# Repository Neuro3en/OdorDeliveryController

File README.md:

# OdorDeliveryController
Arduino shield for odor valve controller

This repo contains the PCB eagle files and the CAM files.
The Arduino code running on the µC

The related research:
https://www.cell.com/cell-reports/pdf/S2211-1247%2820%2930120-0.pdf

Both codes have three program options, identified on the arduino by LED1 ON, LED2 ON, LED1 and 2 ON.
in the script _3odors the three programs indicate the usage of the three odor valves (thus the use of three odors)
in the script A_B_AB, the three programs indicate the usage of valve/odor A, of valve/odor B, and of simultaneous usage of valves/odors AB

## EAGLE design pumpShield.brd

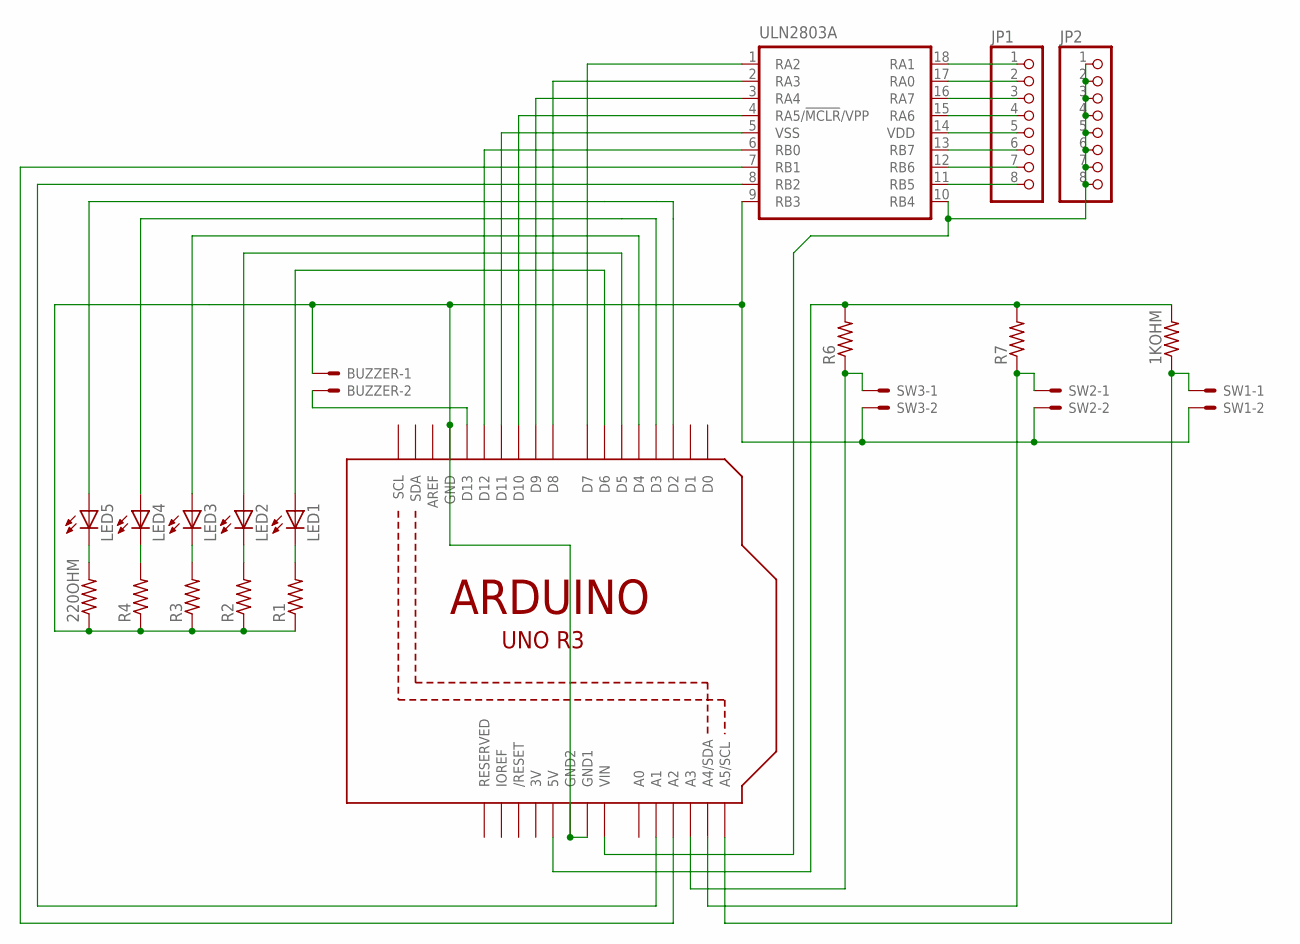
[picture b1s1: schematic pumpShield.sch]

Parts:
1KOHM, 220OHM: R-US_0207/9; 0207/9
BUZZER: 22-23-2021
JP1, JP2: PINHD-1X8CLEANBIG; 1X08-CLEANBIG
LED1, LED2, LED3, LED4, LED5: LED3MM
R1, R2, R3, R4, R6, R7: R-US_0207/9; 0207/9
SW1, SW2, SW3: 22-23-2021
U1: ARDUINOR3-DIMENSION; ARDUINOR3
ULN2803A: PIC16F1826/27P; DIL18

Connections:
3V: U1.3V
unnamed: 220OHM.1, BUZZER.1, R1.1, R2.1, R3.1, R4.1, SW1.2, SW2.2, SW3.2, U1.GND, U1.GND1, U1.GND2, ULN2803A.9 (RB3)
unnamed: JP2.1, JP2.2, JP2.3, JP2.4, JP2.5, JP2.6, JP2.7, JP2.8, U1.VIN, ULN2803A.10 (RB4)
unnamed: LED1.A, U1.D6
unnamed: LED2.A, U1.D5
unnamed: LED3.A, U1.D4
unnamed: LED4.A, U1.D3
unnamed: U1.D7, ULN2803A.1 (RA2)
unnamed: U1.D8, ULN2803A.2 (RA3)
unnamed: U1.D9, ULN2803A.3 (RA4)
unnamed: U1.D10, ULN2803A.4 (RA5/!MCLR!/VPP)
unnamed: U1.D11, ULN2803A.5 (VSS)
unnamed: U1.D12, ULN2803A.6 (RB0)
unnamed: LED1.K (C), R1.2
unnamed: LED2.K (C), R2.2
unnamed: LED3.K (C), R3.2
unnamed: LED4.K (C), R4.2
unnamed: 220OHM.2, LED5.K (C)
unnamed: LED5.A, U1.D2
unnamed: BUZZER.2, U1.D13
unnamed: 1KOHM.2, R6.2, R7.2, U1.5V
unnamed: JP1.8, ULN2803A.11 (RB5)
unnamed: JP1.7, ULN2803A.12 (RB6)
unnamed: JP1.6, ULN2803A.13 (RB7)
unnamed: JP1.5, ULN2803A.14 (VDD)
unnamed: JP1.4, ULN2803A.15 (RA6)
unnamed: JP1.3, ULN2803A.16 (RA7)
unnamed: R6.1, SW3.1, U1.A3
unnamed: R7.1, SW2.1, U1.A4 (A4/SDA)
unnamed: 1KOHM.1, SW1.1, U1.A5 (A5/SCL)
unnamed: U1.A1, ULN2803A.8 (RB2)
unnamed: U1.A2, ULN2803A.7 (RB1)
unnamed: JP1.2, ULN2803A.17 (RA0)
unnamed: JP1.1, ULN2803A.18 (RA1)

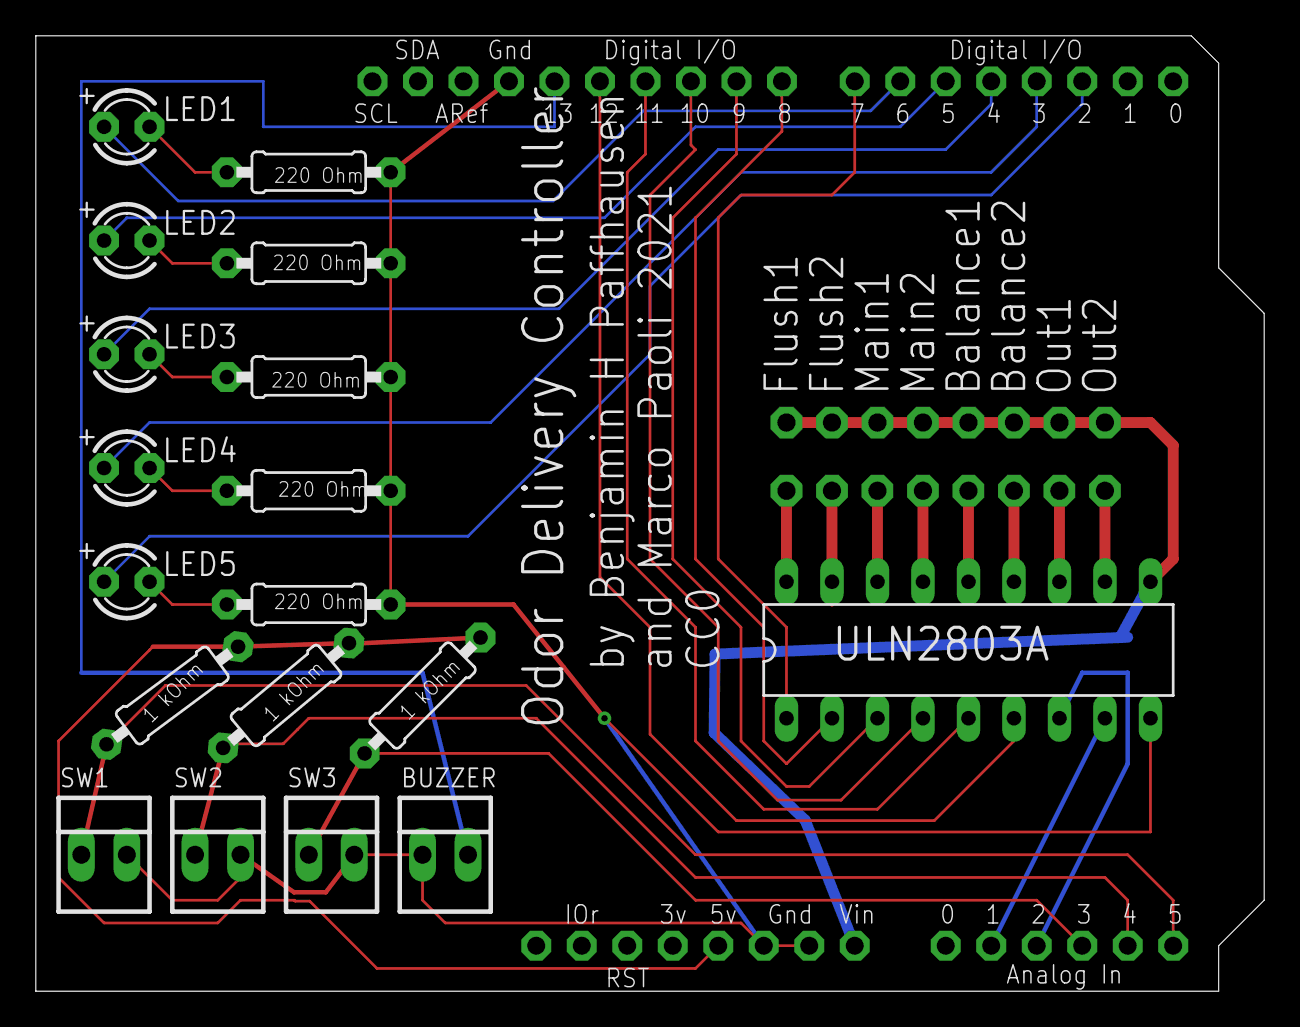
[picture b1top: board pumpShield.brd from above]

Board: 2 copper layers, 68.6 x 53.3 mm, 21 parts (0 on the bottom side), 33 nets.

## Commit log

2021-01-19 Add files via upload
    Eagle files of PCB and .RAR file including the CAM files for upload to PCB manufacturer
2021-01-19 Create LICENSE
2021-01-21 Add files via upload
    Arduino Manual describing the LEDs and Buttons

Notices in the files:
pumpShield.brd:
CC0
